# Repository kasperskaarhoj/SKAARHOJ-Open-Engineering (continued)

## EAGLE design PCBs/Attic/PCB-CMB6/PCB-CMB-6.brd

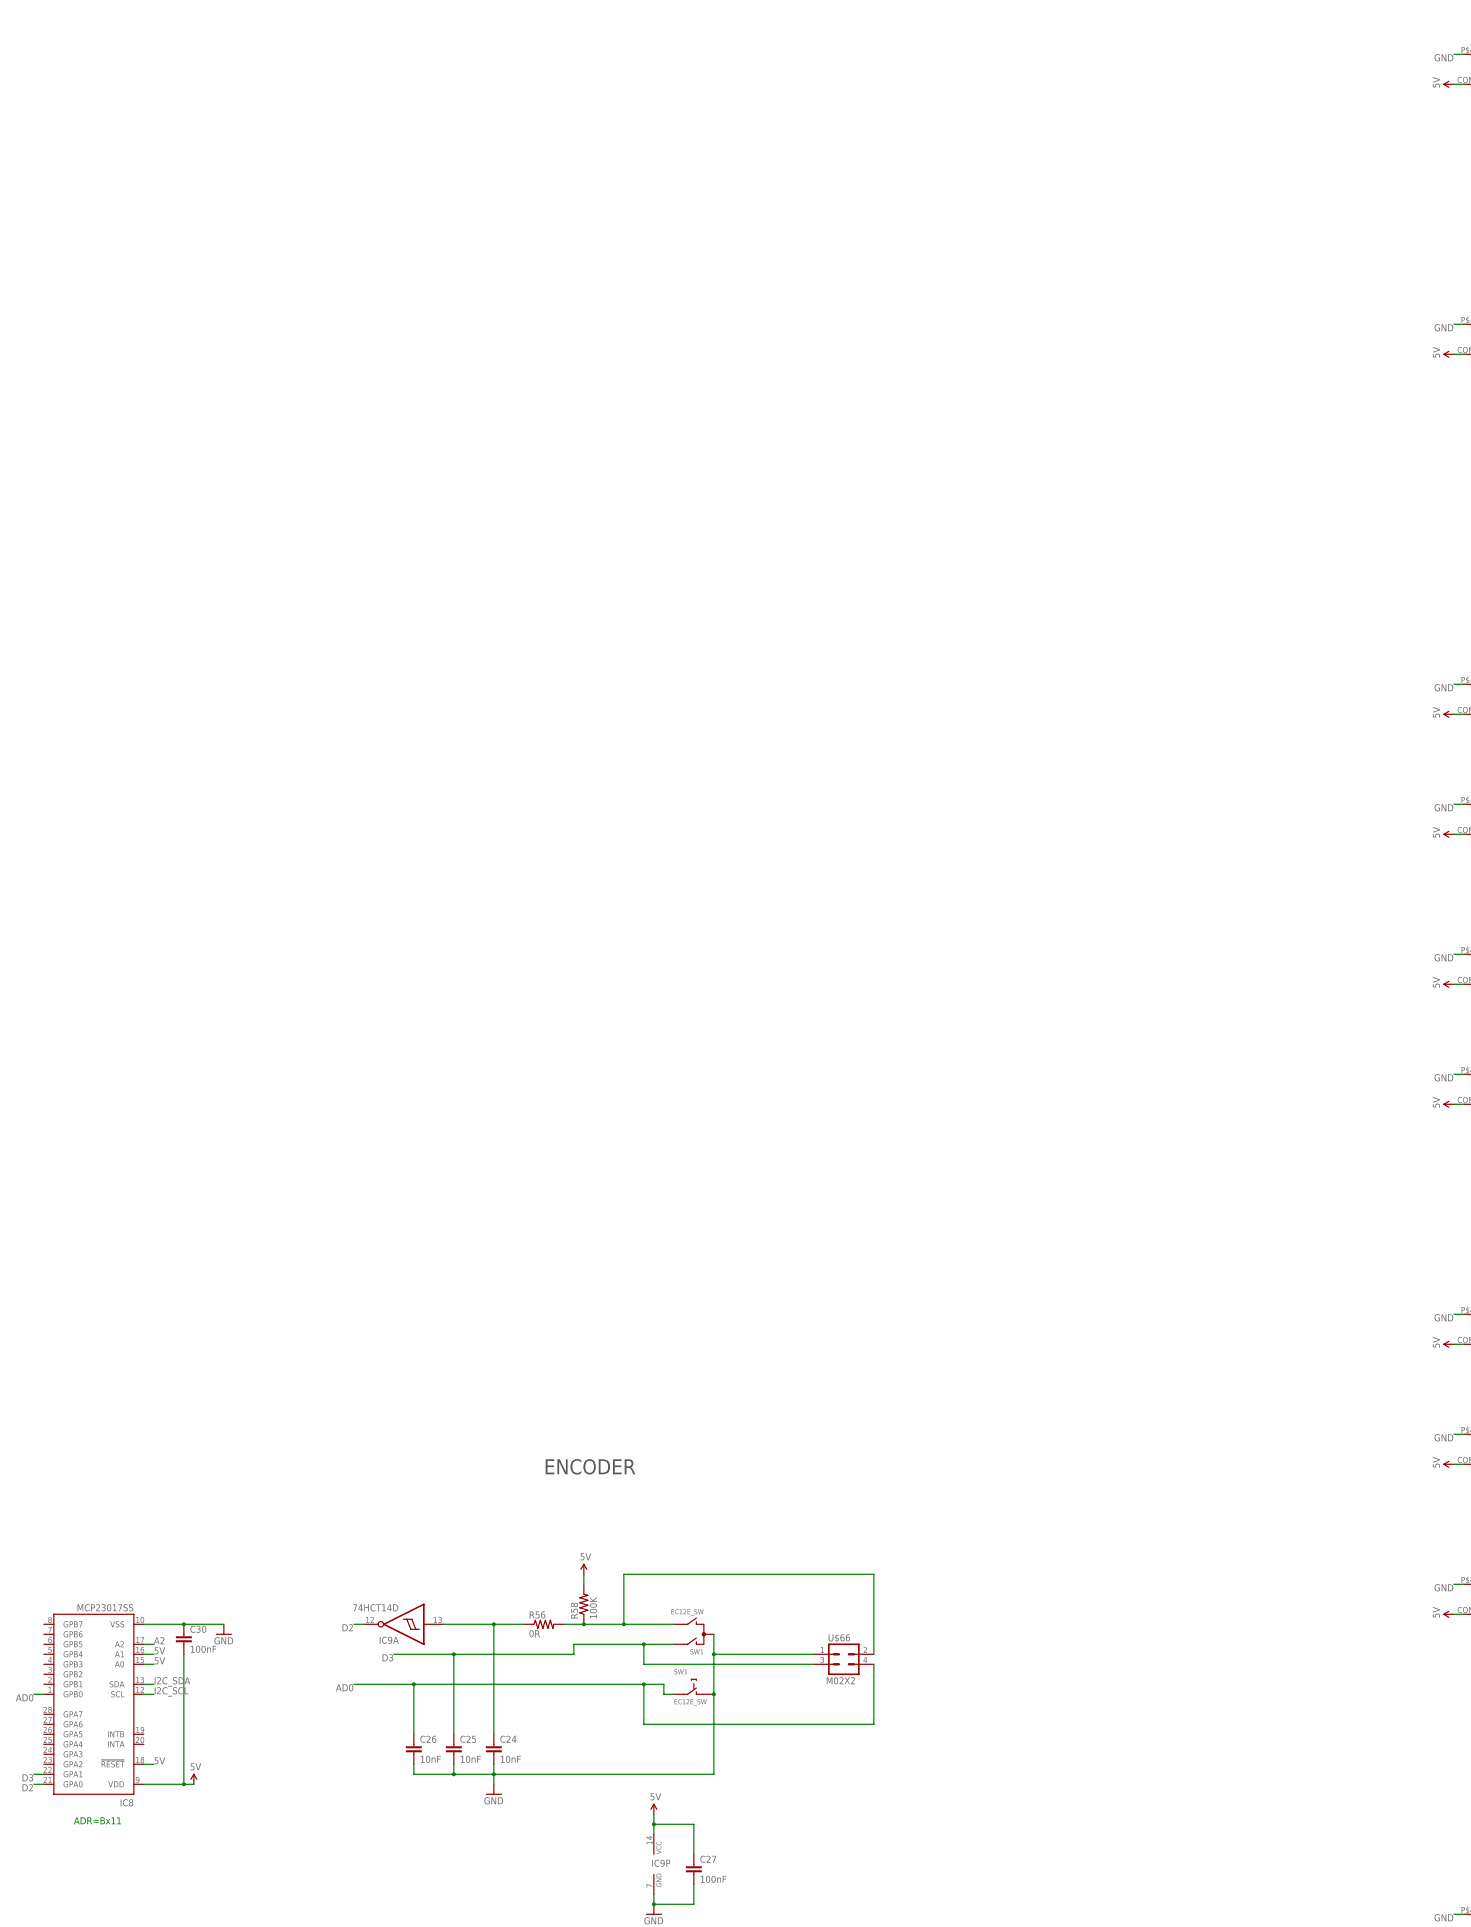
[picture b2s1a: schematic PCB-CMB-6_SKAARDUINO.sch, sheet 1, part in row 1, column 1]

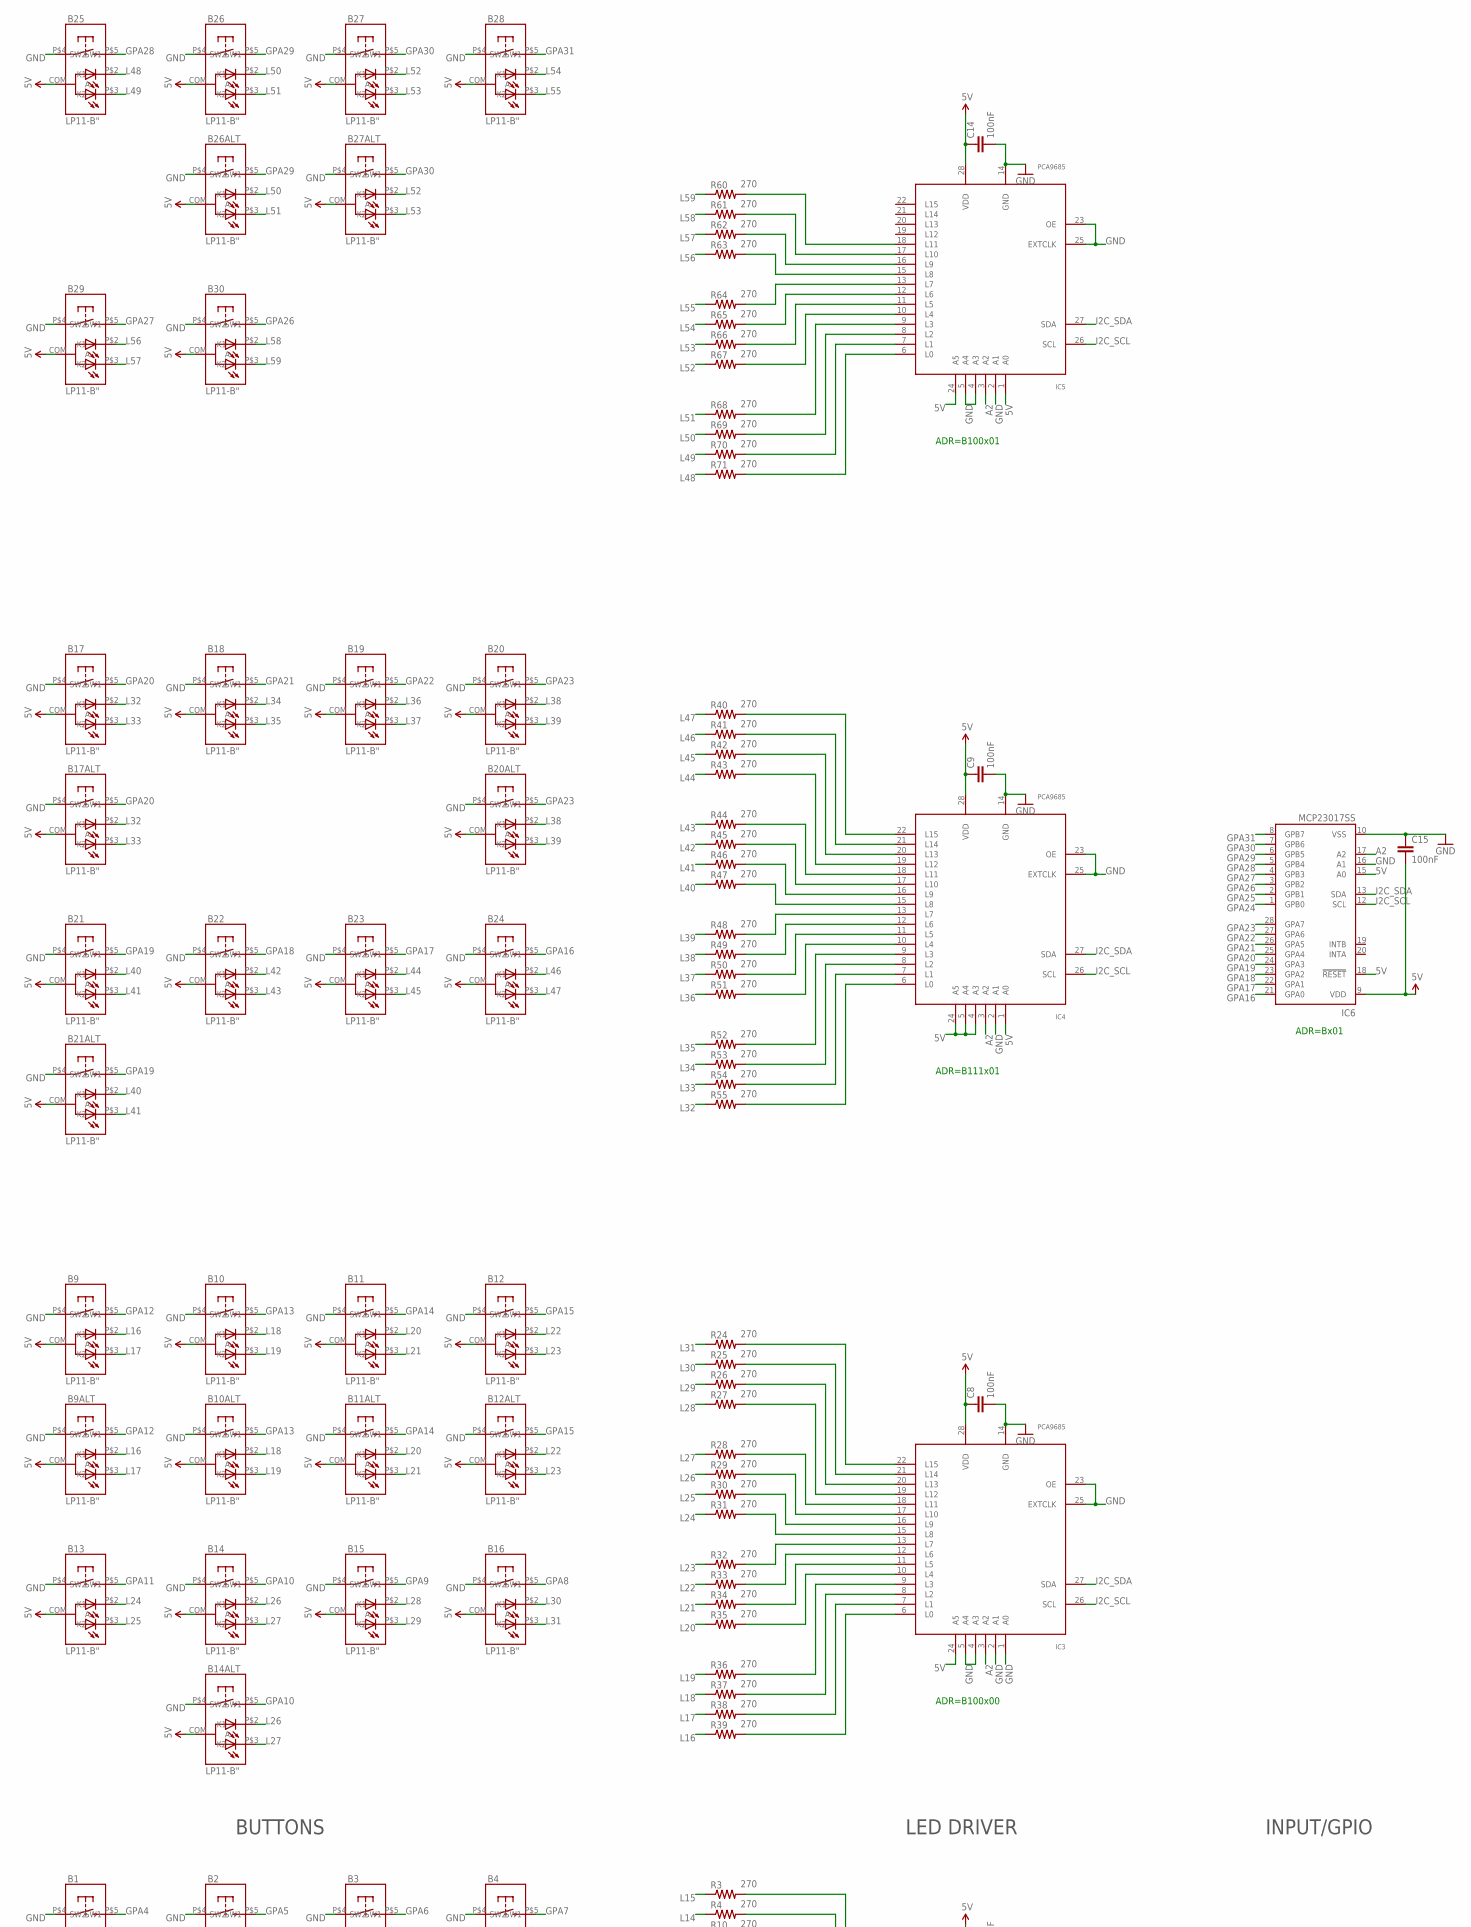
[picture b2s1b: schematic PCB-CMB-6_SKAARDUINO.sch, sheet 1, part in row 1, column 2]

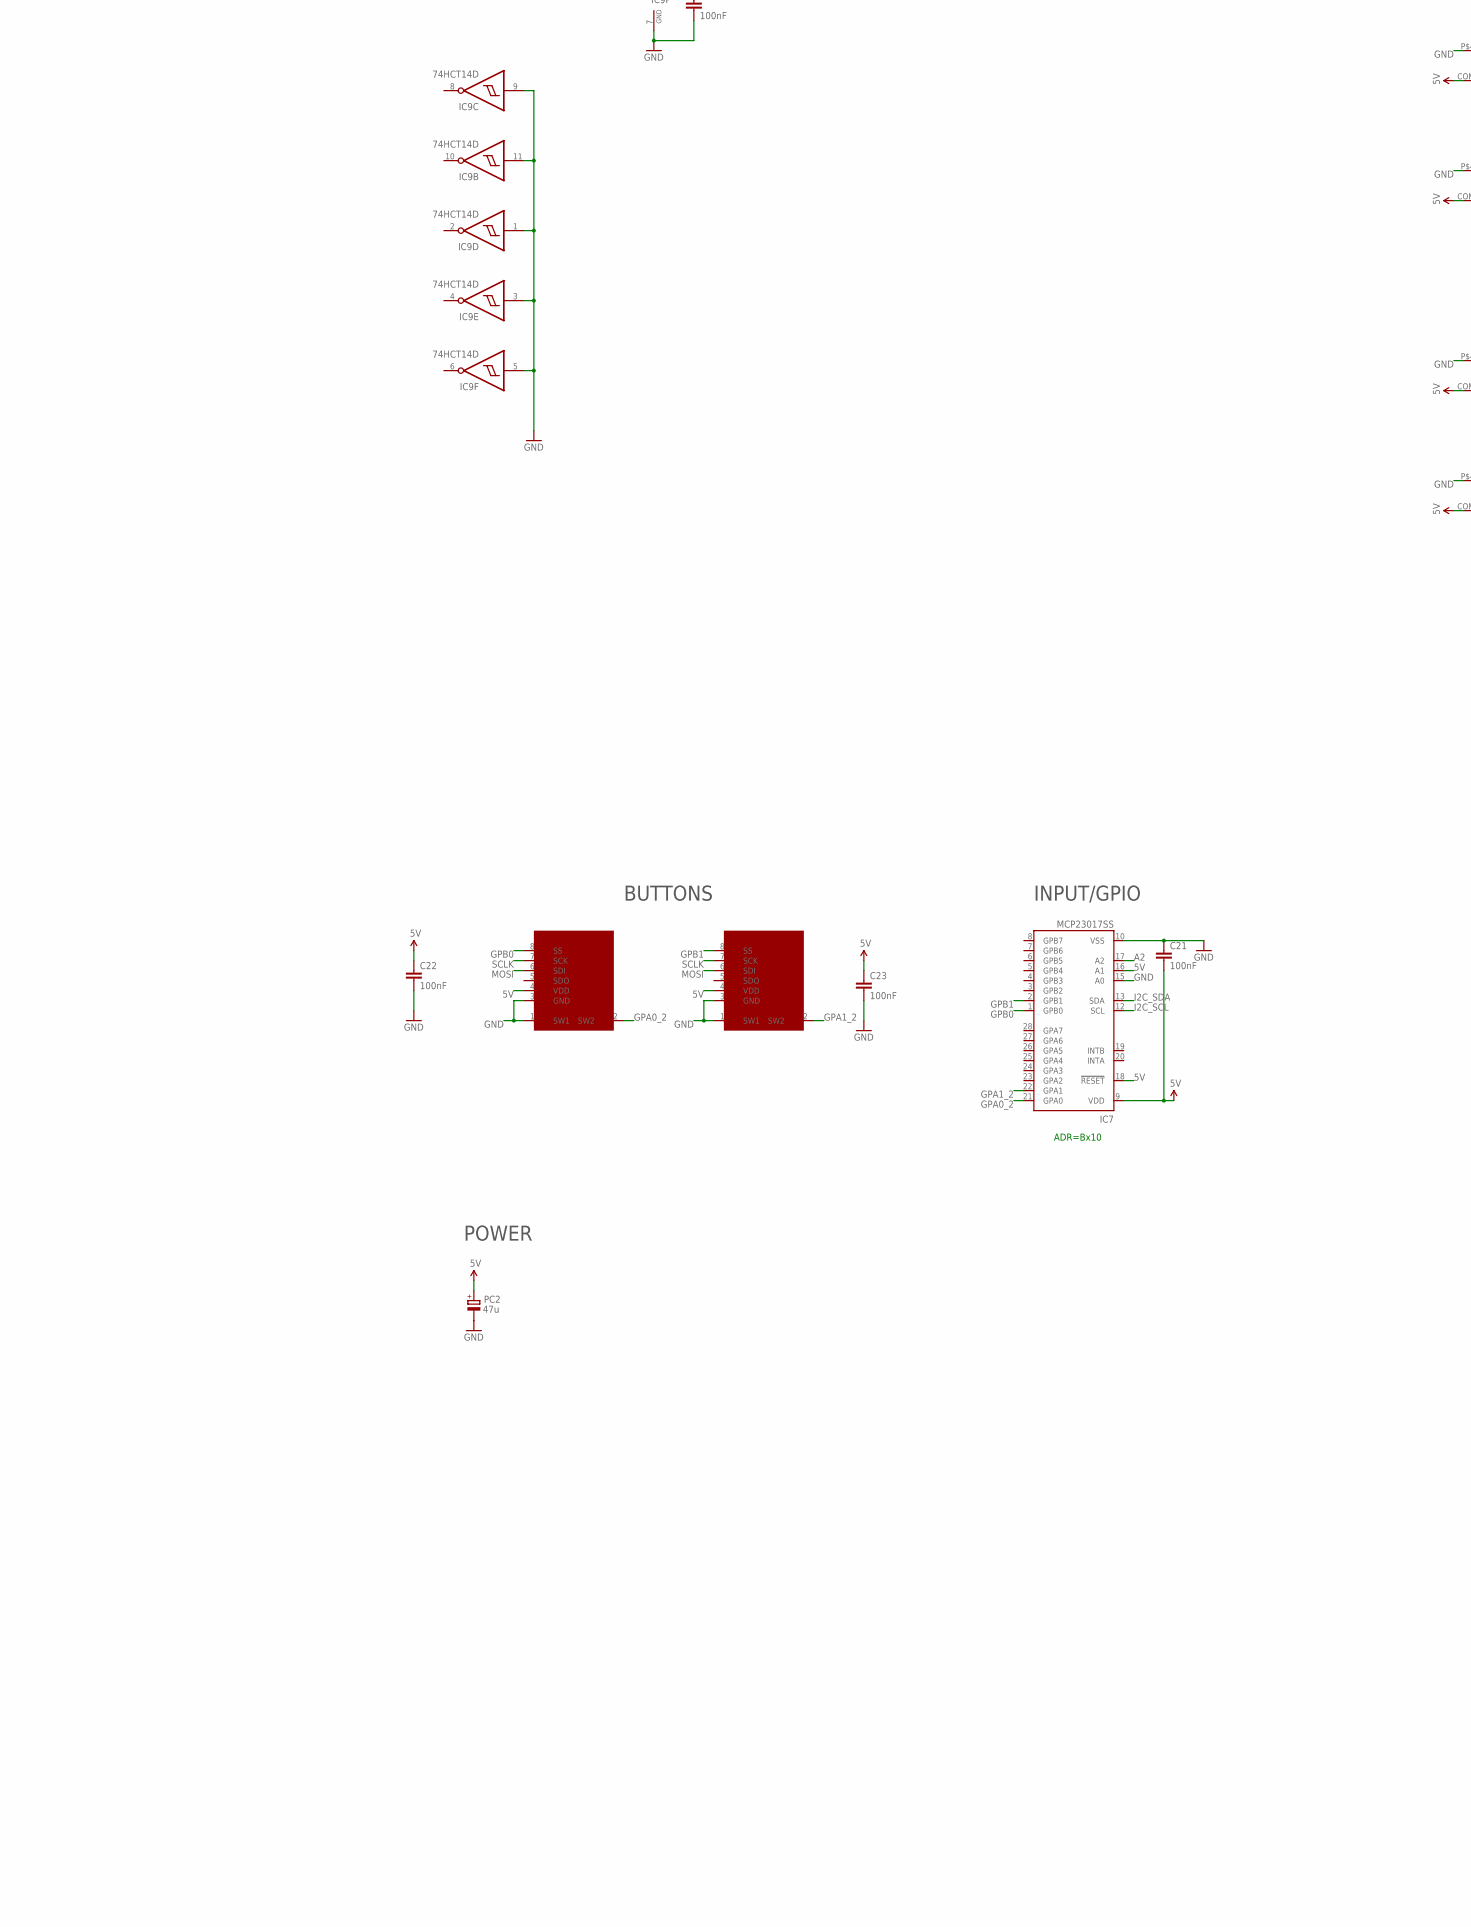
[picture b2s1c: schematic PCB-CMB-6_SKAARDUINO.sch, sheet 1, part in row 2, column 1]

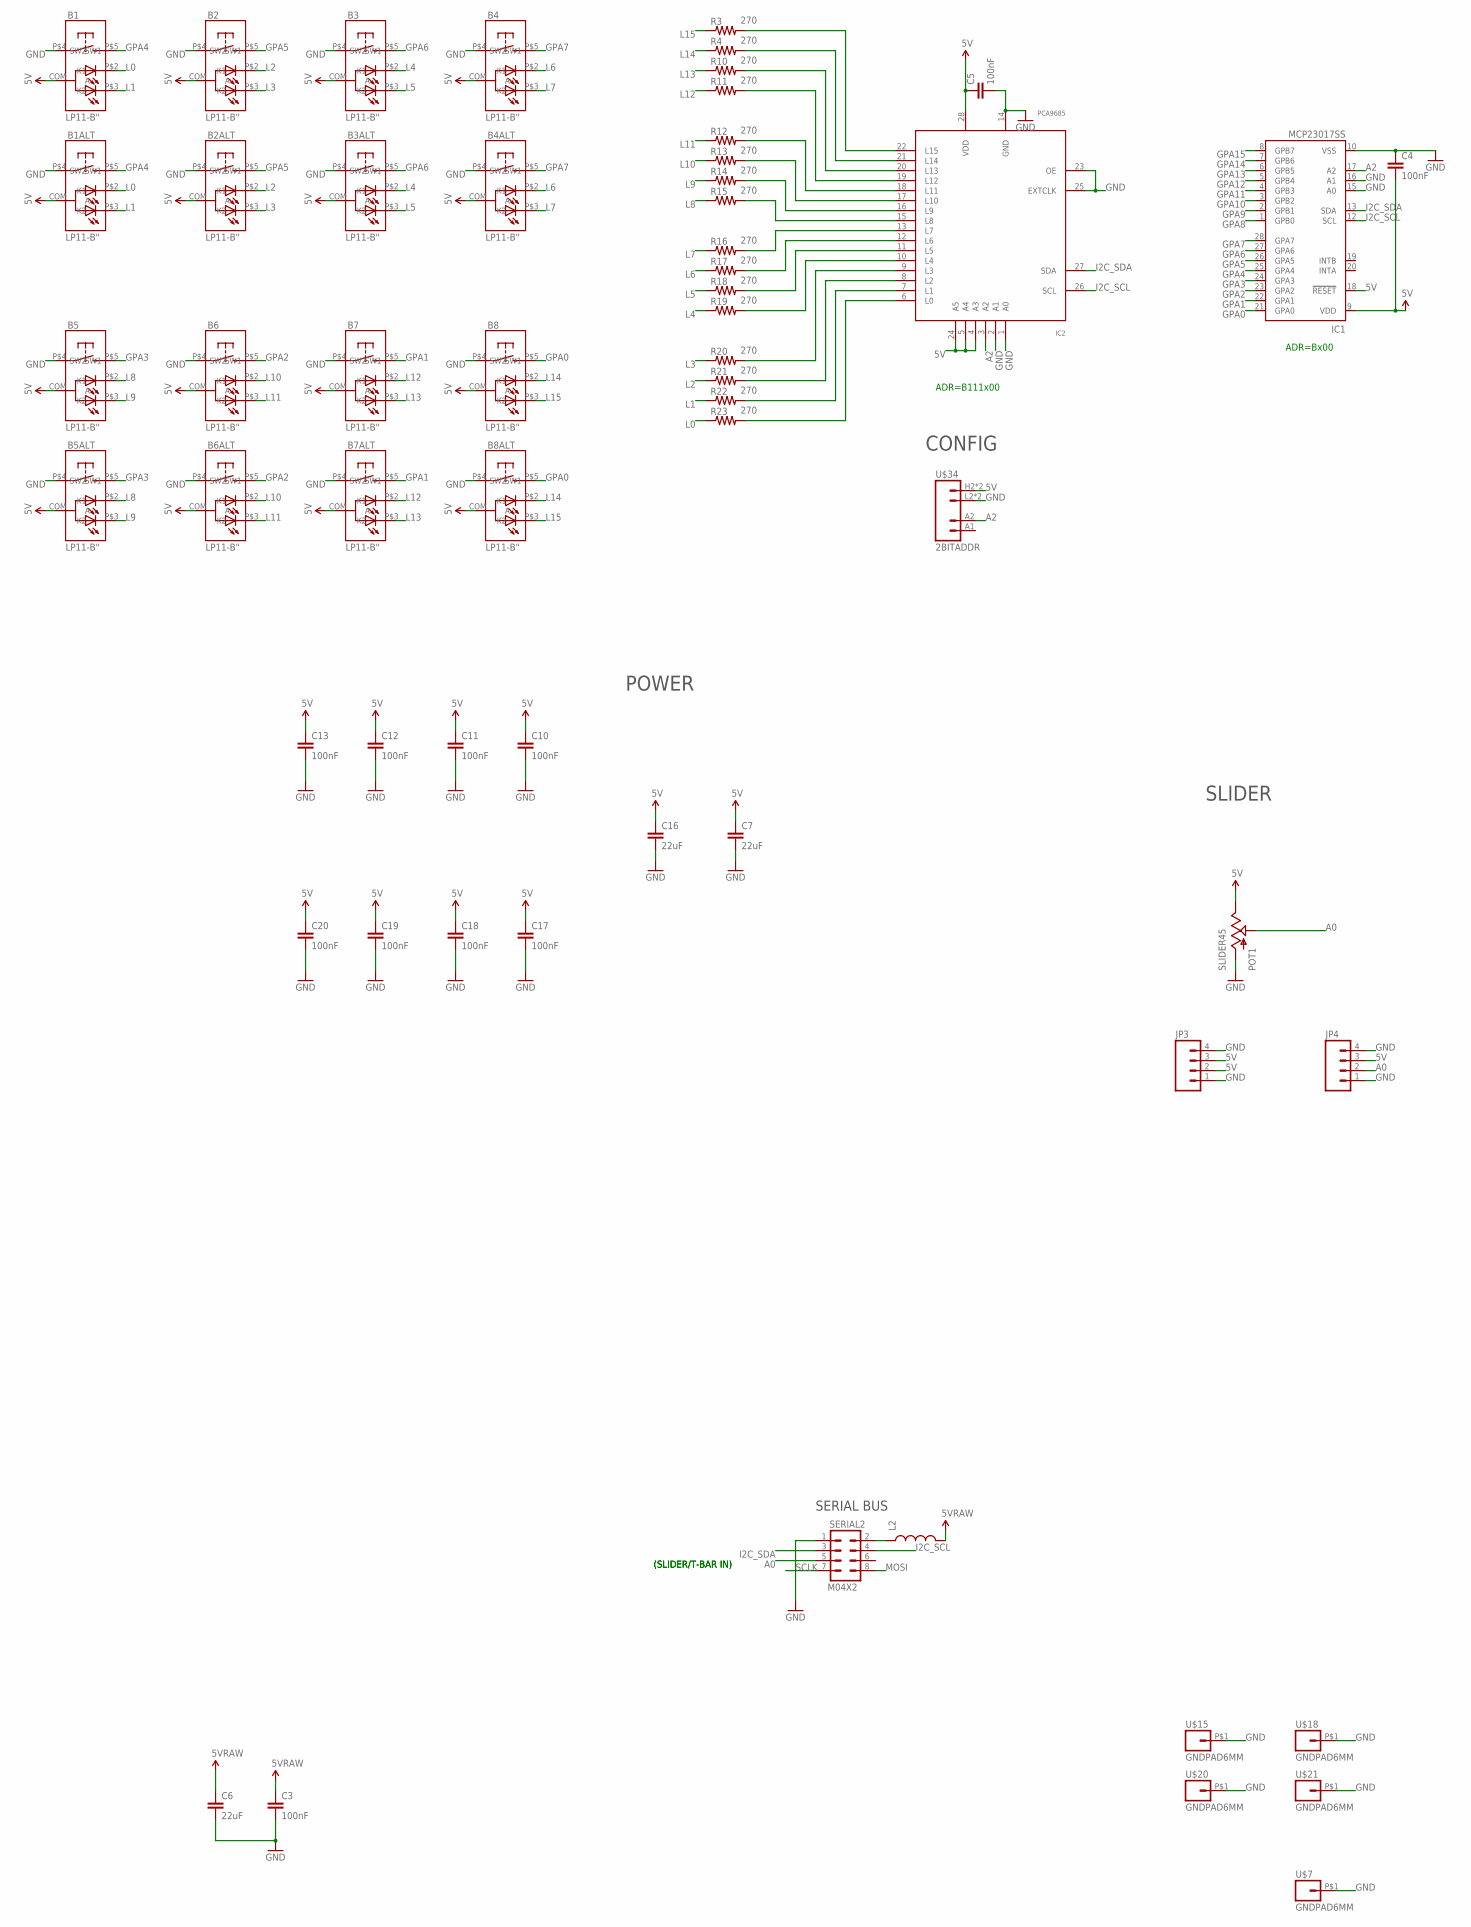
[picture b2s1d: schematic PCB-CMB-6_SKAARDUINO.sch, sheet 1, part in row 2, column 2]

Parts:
B1, B1ALT, B2, B2ALT, B3, B3ALT, B4, B4ALT, B5, B5ALT, B6, B6ALT, B7, B7ALT, B8, B8ALT, B9, B9ALT, B10, B10ALT, B11, B11ALT, B12, B12ALT, B13, B14, B14ALT, B15, B16, B17, B17ALT, B18, B19, B20, B20ALT, B21, B21ALT, B22, B23, B24, B25, B26, B26ALT, B27, B27ALT, B28, B29, B30: LP11-B"; LP11
C3, C4, C5, C8, C9, C10, C11, C12, C13, C14, C15, C17, C18, C19, C20, C21, C22, C23, C27, C30: 100nF; 0603-CAP
C6, C7, C16: 22uF; 0805
C24, C25, C26: 10nF; 0603-CAP
IC1, IC6, IC7, IC8: MCP23017SS; SSOP28; MPN MCP23017-E/SS
IC2, IC3, IC4, IC5: PCA9685; TSSOP28
IC9: 74HCT14D; SO14
JP3, JP4: M04PTH; 1X04
L2: INDUCTOR0805; 0805
PC2: 47u; PANASONIC_D
POT1: SLIDER45
R3, R4, R10, R11, R12, R13, R14, R15, R16, R17, R18, R19, R20, R21, R22, R23, R24, R25, R26, R27, R28, R29, R30, R31, R32, R33, R34, R35, R36, R37, R38, R39, R40, R41, R42, R43, R44, R45, R46, R47, R48, R49, R50, R51, R52, R53, R54, R55, R60, R61, R62, R63, R64, R65, R66, R67, R68, R69, R70, R71: 270; 0603-RES
R56: 0R; 0603-RES
R58: 100K; 0603-RES
SERIAL2: M04X2; 2X4
SSW1, SSW2: SMART_SWITCHSMART_SWITCH_8PIN; SMART_SWITCH
SW1: EC12E_SW; ALPS_EC12E_SW
U$7, U$15, U$18, U$20, U$21: GNDPAD6MM; 3.2MMPAD6MM
U$34: 2BITADDR
U$66: M02X2; 2X2

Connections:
5V: B1.COM (A), B1ALT.COM (A), B2.COM (A), B2ALT.COM (A), B3.COM (A), B3ALT.COM (A), B4.COM (A), B4ALT.COM (A), B5.COM (A), B5ALT.COM (A), B6.COM (A), B6ALT.COM (A), B7.COM (A), B7ALT.COM (A), B8.COM (A), B8ALT.COM (A), B9.COM (A), B9ALT.COM (A), B10.COM (A), B10ALT.COM (A), B11.COM (A), B11ALT.COM (A), B12.COM (A), B12ALT.COM (A), B13.COM (A), B14.COM (A), B14ALT.COM (A), B15.COM (A), B16.COM (A), B17.COM (A), B17ALT.COM (A), B18.COM (A), B19.COM (A), B20.COM (A), B20ALT.COM (A), B21.COM (A), B21ALT.COM (A), B22.COM (A), B23.COM (A), B24.COM (A), B25.COM (A), B26.COM (A), B26ALT.COM (A), B27.COM (A), B27ALT.COM (A), B28.COM (A), B29.COM (A), B30.COM (A), C4.2, C5.1, C7.1, C8.1, C9.1, C10.1, C11.1, C12.1, C13.1, C14.1, C15.2, C16.1, C17.1, C18.1, C19.1, C20.1, C21.2, C22.1, C23.1, C27.1, C30.2, IC1.9 (VDD), IC1.18 (!RESET), IC2.4 (A3), IC2.5 (A4), IC2.24 (A5), IC2.28 (VDD), IC3.24 (A5), IC3.28 (VDD), IC4.1 (A0), IC4.4 (A3), IC4.5 (A4), IC4.24 (A5), IC4.28 (VDD), IC5.1 (A0), IC5.24 (A5), IC5.28 (VDD), IC6.9 (VDD), IC6.15 (A0), IC6.18 (!RESET), IC7.9 (VDD), IC7.16 (A1), IC7.18 (!RESET), IC8.9 (VDD), IC8.15 (A0), IC8.16 (A1), IC8.18 (!RESET), IC9.14 (VCC), JP3.2, JP3.3, JP4.3, PC2.+, POT1.1 (E), R58.2, SSW1.4 (VDD), SSW2.4 (VDD), U$34.H2 (VCC), U$34.H3 (VCC); also elsewhere on the board
5V_RAW: C3.1, C6.1, L2.2; also elsewhere on the board
A0: JP4.2, POT1.2A (S), SERIAL2.5; also elsewhere on the board
A2: IC1.17 (A2), IC2.3 (A2), IC3.3 (A2), IC4.3 (A2), IC5.3 (A2), IC6.17 (A2), IC7.17 (A2), IC8.17 (A2), U$34.A2
AD0: C26.1, IC8.1 (GPB0), SW1.E (2), U$66.4
D2: IC8.21 (GPA0), IC9.12 (O)
D3: C25.1, IC8.22 (GPA1), SW1.A, U$66.3
GND: B1.P$4 (SW1), B1ALT.P$4 (SW1), B2.P$4 (SW1), B2ALT.P$4 (SW1), B3.P$4 (SW1), B3ALT.P$4 (SW1), B4.P$4 (SW1), B4ALT.P$4 (SW1), B5.P$4 (SW1), B5ALT.P$4 (SW1), B6.P$4 (SW1), B6ALT.P$4 (SW1), B7.P$4 (SW1), B7ALT.P$4 (SW1), B8.P$4 (SW1), B8ALT.P$4 (SW1), B9.P$4 (SW1), B9ALT.P$4 (SW1), B10.P$4 (SW1), B10ALT.P$4 (SW1), B11.P$4 (SW1), B11ALT.P$4 (SW1), B12.P$4 (SW1), B12ALT.P$4 (SW1), B13.P$4 (SW1), B14.P$4 (SW1), B14ALT.P$4 (SW1), B15.P$4 (SW1), B16.P$4 (SW1), B17.P$4 (SW1), B17ALT.P$4 (SW1), B18.P$4 (SW1), B19.P$4 (SW1), B20.P$4 (SW1), B20ALT.P$4 (SW1), B21.P$4 (SW1), B21ALT.P$4 (SW1), B22.P$4 (SW1), B23.P$4 (SW1), B24.P$4 (SW1), B25.P$4 (SW1), B26.P$4 (SW1), B26ALT.P$4 (SW1), B27.P$4 (SW1), B27ALT.P$4 (SW1), B28.P$4 (SW1), B29.P$4 (SW1), B30.P$4 (SW1), C3.2, C4.1, C5.2, C6.2, C7.2, C8.2, C9.2, C10.2, C11.2, C12.2, C13.2, C14.2, C15.1, C16.2, C17.2, C18.2, C19.2, C20.2, C21.1, C22.2, C23.2, C24.2, C25.2, C26.2, C27.2, C30.1, IC1.10 (VSS), IC1.15 (A0), IC1.16 (A1), IC2.1 (A0), IC2.2 (A1), IC2.14 (GND), IC2.23 (OE), IC2.25 (EXTCLK), IC3.1 (A0), IC3.2 (A1), IC3.4 (A3), IC3.5 (A4), IC3.14 (GND), IC3.23 (OE), IC3.25 (EXTCLK), IC4.2 (A1), IC4.14 (GND), IC4.23 (OE), IC4.25 (EXTCLK), IC5.2 (A1), IC5.4 (A3), IC5.5 (A4), IC5.14 (GND), IC5.23 (OE), IC5.25 (EXTCLK), IC6.10 (VSS), IC6.16 (A1), IC7.10 (VSS), IC7.15 (A0), IC8.10 (VSS), IC9.1 (I), IC9.3 (I), IC9.5 (I), IC9.7 (GND), IC9.9 (I), IC9.11 (I), JP3.1, JP3.4, JP4.1, JP4.4, PC2.-, POT1.3 (A), SERIAL2.1, SSW1.1 (SW1), SSW1.3 (GND), SSW2.1 (SW1), SSW2.3 (GND), SW1.C, SW1.D (1), U$7.P$1, U$15.P$1, U$18.P$1, U$20.P$1, U$21.P$1, U$34.L2 (GND), U$34.L3 (GND), U$66.1; also elsewhere on the board
GPA0: B8.P$5 (SW2), B8ALT.P$5 (SW2), IC1.21 (GPA0)
GPA0_2: IC7.21 (GPA0), SSW1.2 (SW2)
GPA1: B7.P$5 (SW2), B7ALT.P$5 (SW2), IC1.22 (GPA1)
GPA1_2: IC7.22 (GPA1), SSW2.2 (SW2)
GPA2: B6.P$5 (SW2), B6ALT.P$5 (SW2), IC1.23 (GPA2)
GPA3: B5.P$5 (SW2), B5ALT.P$5 (SW2), IC1.24 (GPA3)
GPA4: B1.P$5 (SW2), B1ALT.P$5 (SW2), IC1.25 (GPA4)
GPA5: B2.P$5 (SW2), B2ALT.P$5 (SW2), IC1.26 (GPA5)
GPA6: B3.P$5 (SW2), B3ALT.P$5 (SW2), IC1.27 (GPA6)
GPA7: B4.P$5 (SW2), B4ALT.P$5 (SW2), IC1.28 (GPA7)
GPA8: B16.P$5 (SW2), IC1.1 (GPB0)
GPA9: B15.P$5 (SW2), IC1.2 (GPB1)
GPA10: B14.P$5 (SW2), B14ALT.P$5 (SW2), IC1.3 (GPB2)
GPA11: B13.P$5 (SW2), IC1.4 (GPB3)
GPA12: B9.P$5 (SW2), B9ALT.P$5 (SW2), IC1.5 (GPB4)
GPA13: B10.P$5 (SW2), B10ALT.P$5 (SW2), IC1.6 (GPB5)
GPA14: B11.P$5 (SW2), B11ALT.P$5 (SW2), IC1.7 (GPB6)
GPA15: B12.P$5 (SW2), B12ALT.P$5 (SW2), IC1.8 (GPB7)
GPA16: B24.P$5 (SW2), IC6.21 (GPA0)
GPA17: B23.P$5 (SW2), IC6.22 (GPA1)
GPA18: B22.P$5 (SW2), IC6.23 (GPA2)
GPA19: B21.P$5 (SW2), B21ALT.P$5 (SW2), IC6.24 (GPA3)
GPA20: B17.P$5 (SW2), B17ALT.P$5 (SW2), IC6.25 (GPA4)
GPA21: B18.P$5 (SW2), IC6.26 (GPA5)
GPA22: B19.P$5 (SW2), IC6.27 (GPA6)
GPA23: B20.P$5 (SW2), B20ALT.P$5 (SW2), IC6.28 (GPA7)
GPA24: IC6.1 (GPB0)
GPA25: IC6.2 (GPB1)
GPA26: B30.P$5 (SW2), IC6.3 (GPB2)
GPA27: B29.P$5 (SW2), IC6.4 (GPB3)
GPA28: B25.P$5 (SW2), IC6.5 (GPB4)
GPA29: B26.P$5 (SW2), B26ALT.P$5 (SW2), IC6.6 (GPB5)
GPA30: B27.P$5 (SW2), B27ALT.P$5 (SW2), IC6.7 (GPB6)
GPA31: B28.P$5 (SW2), IC6.8 (GPB7)
GPB0: IC7.1 (GPB0), SSW1.8 (SS)
GPB1: IC7.2 (GPB1), SSW2.8 (SS)
I2C_SCL: IC1.12 (SCL), IC2.26 (SCL), IC3.26 (SCL), IC4.26 (SCL), IC5.26 (SCL), IC6.12 (SCL), IC7.12 (SCL), IC8.12 (SCL), SERIAL2.4; also elsewhere on the board
I2C_SDA: IC1.13 (SDA), IC2.27 (SDA), IC3.27 (SDA), IC4.27 (SDA), IC5.27 (SDA), IC6.13 (SDA), IC7.13 (SDA), IC8.13 (SDA), SERIAL2.3; also elsewhere on the board
L0: B1.P$2 (K1), B1ALT.P$2 (K1), R23.1
L1: B1.P$3 (K2), B1ALT.P$3 (K2), R22.1
L2: B2.P$2 (K1), B2ALT.P$2 (K1), R21.1
L3: B2.P$3 (K2), B2ALT.P$3 (K2), R20.1
L4: B3.P$2 (K1), B3ALT.P$2 (K1), R19.1
L5: B3.P$3 (K2), B3ALT.P$3 (K2), R18.1
L6: B4.P$2 (K1), B4ALT.P$2 (K1), R17.1
L7: B4.P$3 (K2), B4ALT.P$3 (K2), R16.1
L8: B5.P$2 (K1), B5ALT.P$2 (K1), R15.1
L9: B5.P$3 (K2), B5ALT.P$3 (K2), R14.1
L10: B6.P$2 (K1), B6ALT.P$2 (K1), R13.1
L11: B6.P$3 (K2), B6ALT.P$3 (K2), R12.1
L12: B7.P$2 (K1), B7ALT.P$2 (K1), R11.1
L13: B7.P$3 (K2), B7ALT.P$3 (K2), R10.1
L14: B8.P$2 (K1), B8ALT.P$2 (K1), R4.1
L15: B8.P$3 (K2), B8ALT.P$3 (K2), R3.1
L16: B9.P$2 (K1), B9ALT.P$2 (K1), R39.1
L17: B9.P$3 (K2), B9ALT.P$3 (K2), R38.1
L18: B10.P$2 (K1), B10ALT.P$2 (K1), R37.1
L19: B10.P$3 (K2), B10ALT.P$3 (K2), R36.1
L20: B11.P$2 (K1), B11ALT.P$2 (K1), R35.1
L21: B11.P$3 (K2), B11ALT.P$3 (K2), R34.1
L22: B12.P$2 (K1), B12ALT.P$2 (K1), R33.1
L23: B12.P$3 (K2), B12ALT.P$3 (K2), R32.1
L24: B13.P$2 (K1), R31.1
L25: B13.P$3 (K2), R30.1
L26: B14.P$2 (K1), B14ALT.P$2 (K1), R29.1
L27: B14.P$3 (K2), B14ALT.P$3 (K2), R28.1
L28: B15.P$2 (K1), R27.1
L29: B15.P$3 (K2), R26.1
L30: B16.P$2 (K1), R25.1
L31: B16.P$3 (K2), R24.1
L32: B17.P$2 (K1), B17ALT.P$2 (K1), R55.1
L33: B17.P$3 (K2), B17ALT.P$3 (K2), R54.1
L34: B18.P$2 (K1), R53.1
L35: B18.P$3 (K2), R52.1
L36: B19.P$2 (K1), R51.1
L37: B19.P$3 (K2), R50.1
L38: B20.P$2 (K1), B20ALT.P$2 (K1), R49.1
L39: B20.P$3 (K2), B20ALT.P$3 (K2), R48.1
L40: B21.P$2 (K1), B21ALT.P$2 (K1), R47.1
L41: B21.P$3 (K2), B21ALT.P$3 (K2), R46.1
L42: B22.P$2 (K1), R45.1
L43: B22.P$3 (K2), R44.1
L44: B23.P$2 (K1), R43.1
L45: B23.P$3 (K2), R42.1
L46: B24.P$2 (K1), R41.1
L47: B24.P$3 (K2), R40.1
L48: B25.P$2 (K1), R71.1
L49: B25.P$3 (K2), R70.1
L50: B26.P$2 (K1), B26ALT.P$2 (K1), R69.1
L51: B26.P$3 (K2), B26ALT.P$3 (K2), R68.1
L52: B27.P$2 (K1), B27ALT.P$2 (K1), R67.1
L53: B27.P$3 (K2), B27ALT.P$3 (K2), R66.1
L54: B28.P$2 (K1), R65.1
L55: B28.P$3 (K2), R64.1
L56: B29.P$2 (K1), R63.1
L57: B29.P$3 (K2), R62.1
L58: B30.P$2 (K1), R61.1
L59: B30.P$3 (K2), R60.1
MOSI: SERIAL2.8, SSW1.6 (SDI), SSW2.6 (SDI); also elsewhere on the board
unnamed: L2.1, SERIAL2.2
unnamed: R56.2, R58.1, SW1.B, U$66.2
unnamed: IC2.13 (L7), R16.2
unnamed: IC2.12 (L6), R17.2
unnamed: IC2.11 (L5), R18.2
unnamed: IC2.10 (L4), R19.2
unnamed: IC2.9 (L3), R20.2
unnamed: IC2.8 (L2), R21.2
unnamed: IC2.7 (L1), R22.2
unnamed: IC2.6 (L0), R23.2
unnamed: IC2.15 (L8), R15.2
unnamed: IC2.16 (L9), R14.2
unnamed: IC2.17 (L10), R13.2
unnamed: IC2.18 (L11), R12.2
unnamed: IC2.19 (L12), R11.2
unnamed: IC2.20 (L13), R10.2
unnamed: IC2.21 (L14), R4.2
unnamed: IC2.22 (L15), R3.2
unnamed: IC3.13 (L7), R32.2
unnamed: IC3.12 (L6), R33.2
unnamed: IC3.11 (L5), R34.2
unnamed: IC3.10 (L4), R35.2
unnamed: IC3.9 (L3), R36.2
unnamed: IC3.8 (L2), R37.2
unnamed: IC3.7 (L1), R38.2
unnamed: IC3.6 (L0), R39.2
unnamed: IC3.15 (L8), R31.2
unnamed: IC3.16 (L9), R30.2
unnamed: IC3.17 (L10), R29.2
unnamed: IC3.18 (L11), R28.2
unnamed: IC3.19 (L12), R27.2
unnamed: IC3.20 (L13), R26.2
unnamed: IC3.21 (L14), R25.2
unnamed: IC3.22 (L15), R24.2
unnamed: IC4.13 (L7), R48.2
unnamed: IC4.12 (L6), R49.2
unnamed: IC4.11 (L5), R50.2
unnamed: IC4.10 (L4), R51.2
unnamed: IC4.9 (L3), R52.2
unnamed: IC4.8 (L2), R53.2
unnamed: IC4.7 (L1), R54.2
unnamed: IC4.6 (L0), R55.2
unnamed: IC4.15 (L8), R47.2
unnamed: IC4.16 (L9), R46.2
unnamed: IC4.17 (L10), R45.2
unnamed: IC4.18 (L11), R44.2
unnamed: IC4.19 (L12), R43.2
unnamed: IC4.20 (L13), R42.2
unnamed: IC4.21 (L14), R41.2
unnamed: IC4.22 (L15), R40.2
unnamed: IC5.13 (L7), R64.2
unnamed: IC5.12 (L6), R65.2
unnamed: IC5.11 (L5), R66.2
unnamed: IC5.10 (L4), R67.2
unnamed: IC5.9 (L3), R68.2
unnamed: IC5.8 (L2), R69.2
unnamed: IC5.7 (L1), R70.2
unnamed: IC5.6 (L0), R71.2
unnamed: IC5.15 (L8), R63.2
unnamed: IC5.16 (L9), R62.2
unnamed: IC5.17 (L10), R61.2
unnamed: IC5.18 (L11), R60.2
unnamed: C24.1, IC9.13 (I), R56.1
SCLK: SERIAL2.7, SSW1.7 (SCK), SSW2.7 (SCK); also elsewhere on the board

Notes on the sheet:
SERIAL BUS
(SLIDER/T-BAR IN)
ADR=B111x00
ADR=Bx00
BUTTONS
LED DRIVER
INPUT/GPIO
POWER
CONFIG
ADR=B100x00
ADR=B111x01
ADR=B100x01
ADR=Bx01
SLIDER
ENCODER
ADR=Bx10
ADR=Bx11

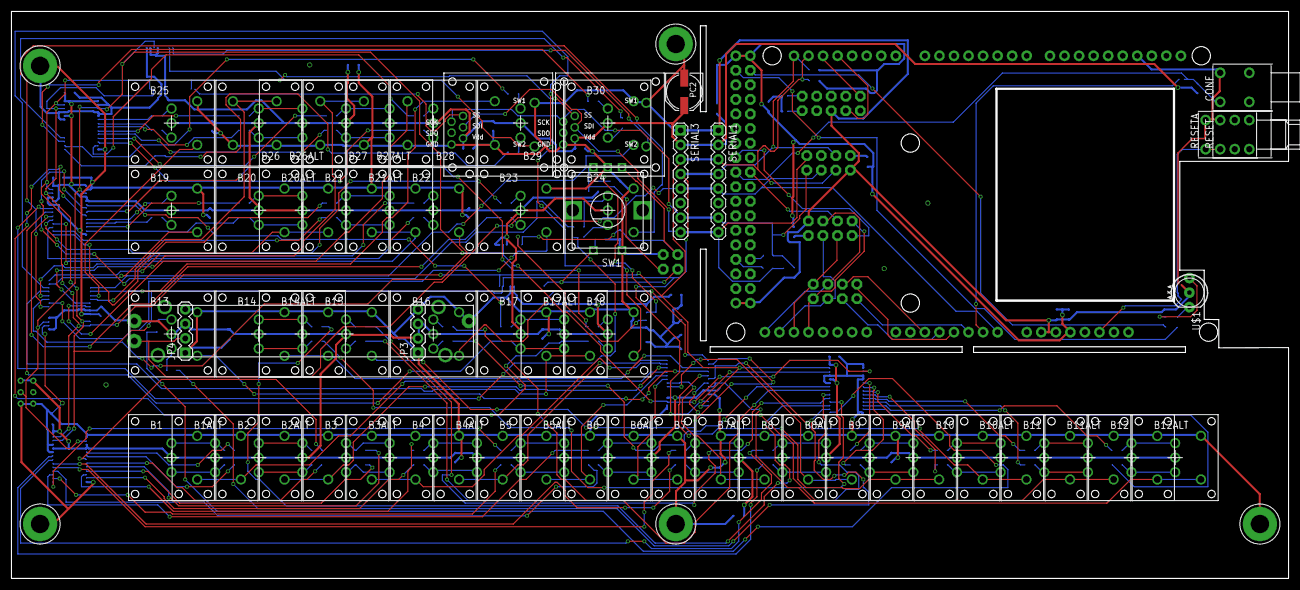
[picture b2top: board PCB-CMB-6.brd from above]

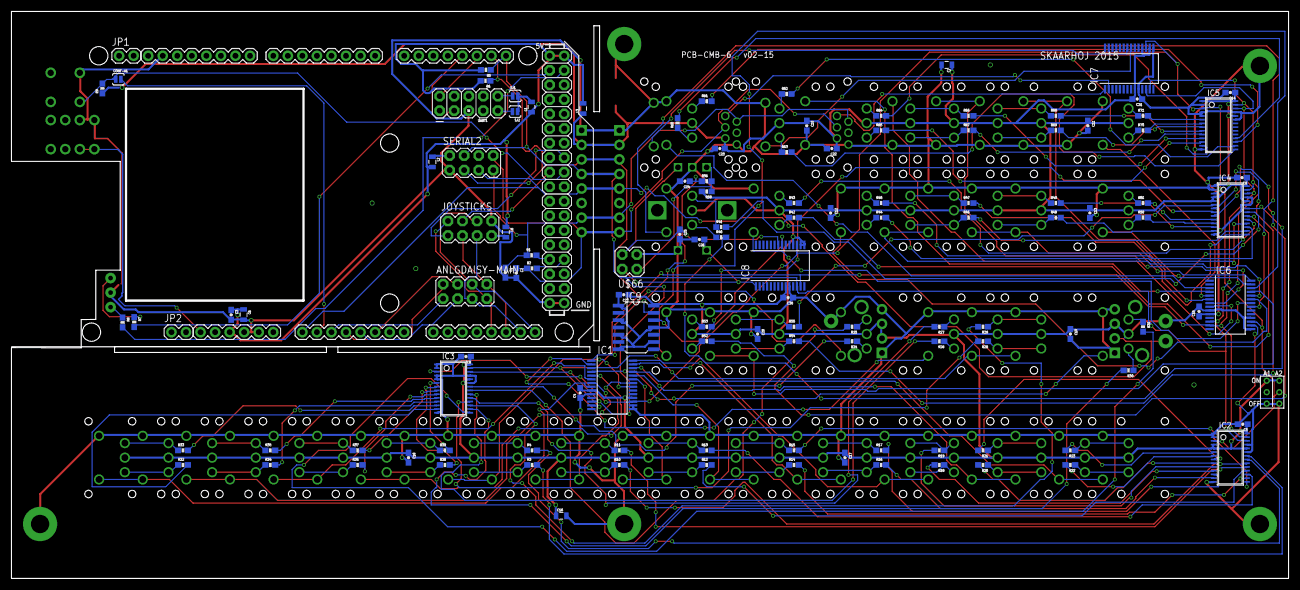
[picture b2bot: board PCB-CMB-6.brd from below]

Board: 2 copper layers, 223.0 x 99.0 mm, 188 parts (122 on the bottom side), 194 nets.

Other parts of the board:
ANLGDAISY-MAIN: M04X2; 2X4
C1, C2: 220pF?; 0603-CAP
CONF: PUSHBUTTON
CONF-A1: SOLDERJUMPERNO; SJ_2S-NO
JOYSTICKS: M04X2; 2X4
JP1, JP2: 1X02
L1, L3, L6: 0805
R1, R2: ?; 0603-RES
R5, R6: 1K5; 0603-RES
R7, R8: 270R; 0603-RES
R9: 10K; 0603-RES
RESET: PUSHBUTTON
RESETA: PUSHBUTTON
SERIAL1, SERIAL3: 1X08
SJ1, SJ2: SOLDERJUMPERNO; SJ_2S-NO
U1: ARDUINO-MEGAFULL; ARDUINO_MEGA
U$1: LEDBICOLOR-AKA; LED5MM-BICOLOR
UART1: M05X2PTH; AVR_ICSP

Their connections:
5V: L3.1, R9.1, SERIAL1.2, SERIAL3.2; also elsewhere on the board
5V_RAW: L1.1, L3.2, L6.1, R5.2, R6.2, U1.5V@0, U1.5V@1, U1.5V@2; also elsewhere on the board
A0: SERIAL1.5, SERIAL3.5, U1.A0; also elsewhere on the board
A1: CONF-A1.2, U1.A1
A3: ANLGDAISY-MAIN.2, U1.A3
A4: ANLGDAISY-MAIN.3, U1.A4
A5: ANLGDAISY-MAIN.4, U1.A5
A12: ANLGDAISY-MAIN.7, JOYSTICKS.2, U1.A12
A13: ANLGDAISY-MAIN.8, JOYSTICKS.3, U1.A13
A14: ANLGDAISY-MAIN.5, JOYSTICKS.5, U1.A14
A15: ANLGDAISY-MAIN.6, JOYSTICKS.6, U1.A15
AN2: ANLGDAISY-MAIN.1, U1.A2
D22: R7.2, U1.22
D23: R8.2, U1.23
D37: CONF.3, CONF-A1.1, R9.2, U1.37
GND: C1.2, C2.2, CONF.1, JOYSTICKS.8, RESET.1, RESETA.1, SERIAL1.1, SERIAL3.1, U1.GND@0, U1.GND@1, U1.GND@2, U1.GND@3, U1.GND@4, U$1.K1, UART1.5; also elsewhere on the board
I2C_SCL: R5.1, SERIAL1.4, SERIAL3.4, U1.21; also elsewhere on the board
I2C_SDA: R6.1, SERIAL1.3, SERIAL3.3, U1.20; also elsewhere on the board
MOSI: C2.1, R2.1, SERIAL1.8, SERIAL3.8; also elsewhere on the board
unnamed: L1.2, SJ1.2, SJ2.1
unnamed: JOYSTICKS.7, L6.2
unnamed: SJ2.2, UART1.9
unnamed: SJ1.1, UART1.10
unnamed: R1.2, U1.48
unnamed: R2.2, U1.49
unnamed: R7.1, U$1.A3
unnamed: R8.1, U$1.A2
RESET: RESET.3, RESETA.3, U1.RESET
RXD1: U1.19, UART1.2
SCLK: C1.1, R1.1, SERIAL1.7, SERIAL3.7; also elsewhere on the board
SW1: JOYSTICKS.1, U1.35
SW2: JOYSTICKS.4, U1.36
TXD1: U1.18, UART1.3
